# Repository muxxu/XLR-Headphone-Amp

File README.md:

## Symmetric XLR Headphone Amplifier

In this repo you will find a headphone amplifier mainly developed for in-ear monitoring.

The amplifier is designed to be driven with symmetrical audio signals connected via XLR. It converts the symmetrical signals (Left and Right for stereo or only Right for mono, switchable) to an unsymmetrical signal. This signal is further amplified to drive headphones or in-ears. Beside the complete eagle schematics and board files, the repo contains a 3D printable casing. It is designed so that it can be attached to your belt. The amplifier is powered by 2-AA battery cells. These should last easily 50 hours, so enough time for some band sessions or concerts.

If you are interested in building one or have any questions feel free to contact me.

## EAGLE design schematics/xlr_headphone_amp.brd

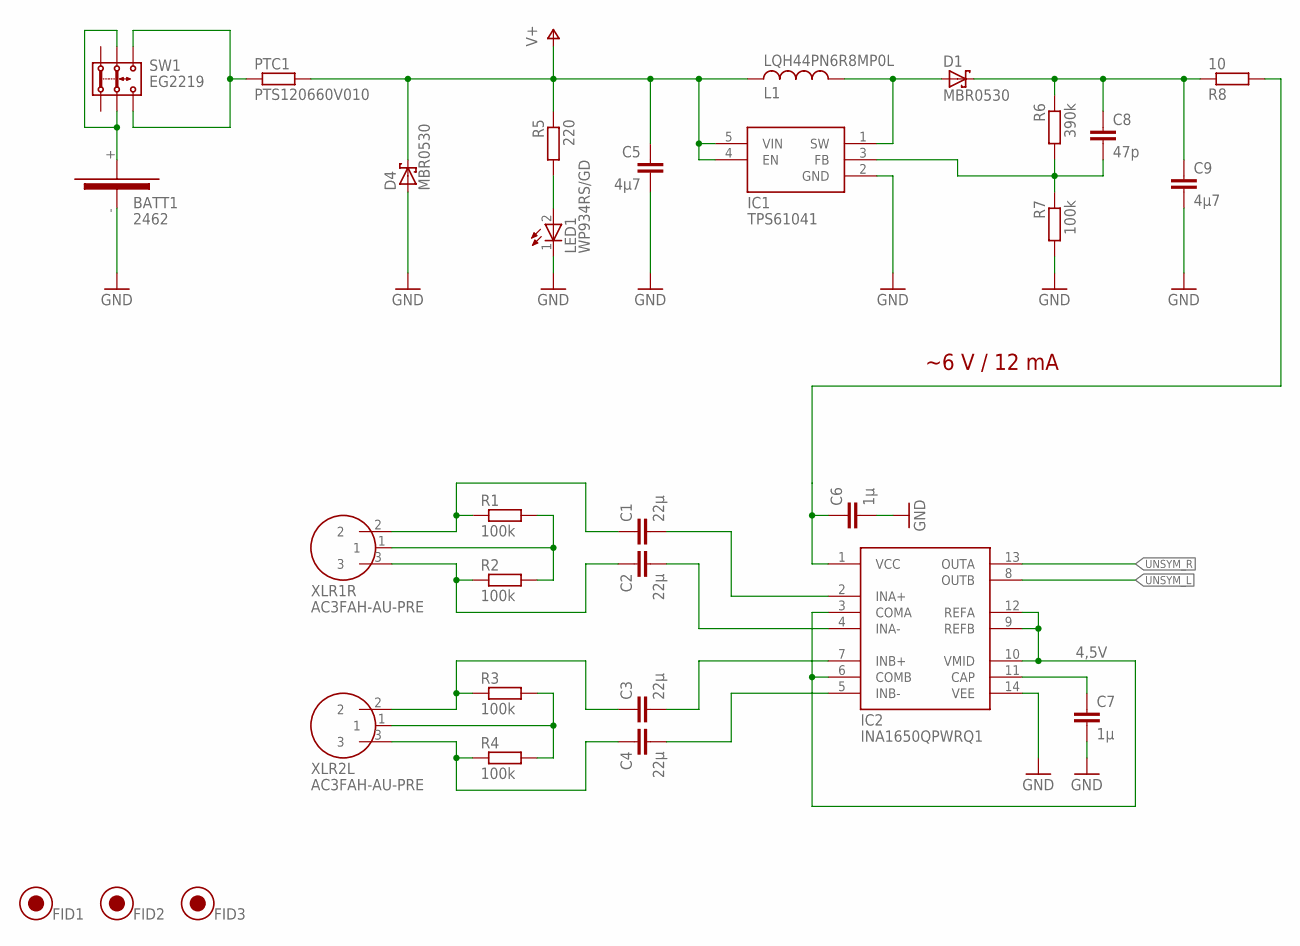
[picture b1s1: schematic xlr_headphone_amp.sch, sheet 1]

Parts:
BATT1: 2462
C1, C2, C3, C4: 22µ; C1206
C5, C9: 4µ7; C1206
C6, C7: 1µ; C1206
C8: 47p; C1206
D1, D4: MBR0530; SOD123
FID1, FID2, FID3: FIDICUAL
IC1: TPS61041; SOT23-5
IC2: INA1650QPWRQ1; R-PDSO-G14
L1: LQH44PN6R8MP0L; L1515(4040)
LED1: WP934RS/GD; WP934
PTC1: PTS120660V010; R1206
R1, R2, R3, R4, R7: 100k; R1206
R5: 220; R1206
R6: 390k; R1206
R8: 10; R1206
SW1: EG2219
XLR1R, XLR2L: AC3FAH-AU-PRE; AC3FAH

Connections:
4,5V: IC2.3 (COMA), IC2.6 (COMB), IC2.9 (REFB), IC2.10 (VMID), IC2.12 (REFA)
GND: BATT1.- (NEG), C5.2, C6.2, C7.2, C9.2, D4.A, IC1.2 (GND), IC2.14 (VEE), LED1.1 (C), R7.2; also elsewhere on the board
unnamed: R1.2, R2.2, XLR1R.1
unnamed: C1.1, R1.1, XLR1R.2
unnamed: C2.1, R2.1, XLR1R.3
unnamed: C1.2, IC2.2 (INA+)
unnamed: C2.2, IC2.4 (INA-)
unnamed: R3.2, R4.2, XLR2L.1
unnamed: C3.1, R3.1, XLR2L.2
unnamed: C4.1, R4.1, XLR2L.3
unnamed: C3.2, IC2.7 (INB+)
unnamed: C4.2, IC2.5 (INB-)
unnamed: C7.1, IC2.11 (CAP)
unnamed: LED1.2 (A), R5.2
unnamed: D1.A, IC1.1 (SW), L1.1
unnamed: C8.2, IC1.3 (FB), R6.2, R7.1
unnamed: C8.1, C9.1, D1.C, R6.1, R8.1
unnamed: BATT1.+ (POS), SW1.B1, SW1.B2
unnamed: PTC1.1, SW1.C1, SW1.C2
unnamed: C6.1, IC2.1 (VCC), R8.2
UNSYM_L: IC2.8 (OUTB); also elsewhere on the board
UNSYM_R: IC2.13 (OUTA); also elsewhere on the board
V+: C5.1, D4.C, IC1.4 (EN), IC1.5 (VIN), L1.2, PTC1.2, R5.1; also elsewhere on the board

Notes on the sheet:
~6 V / 12 mA

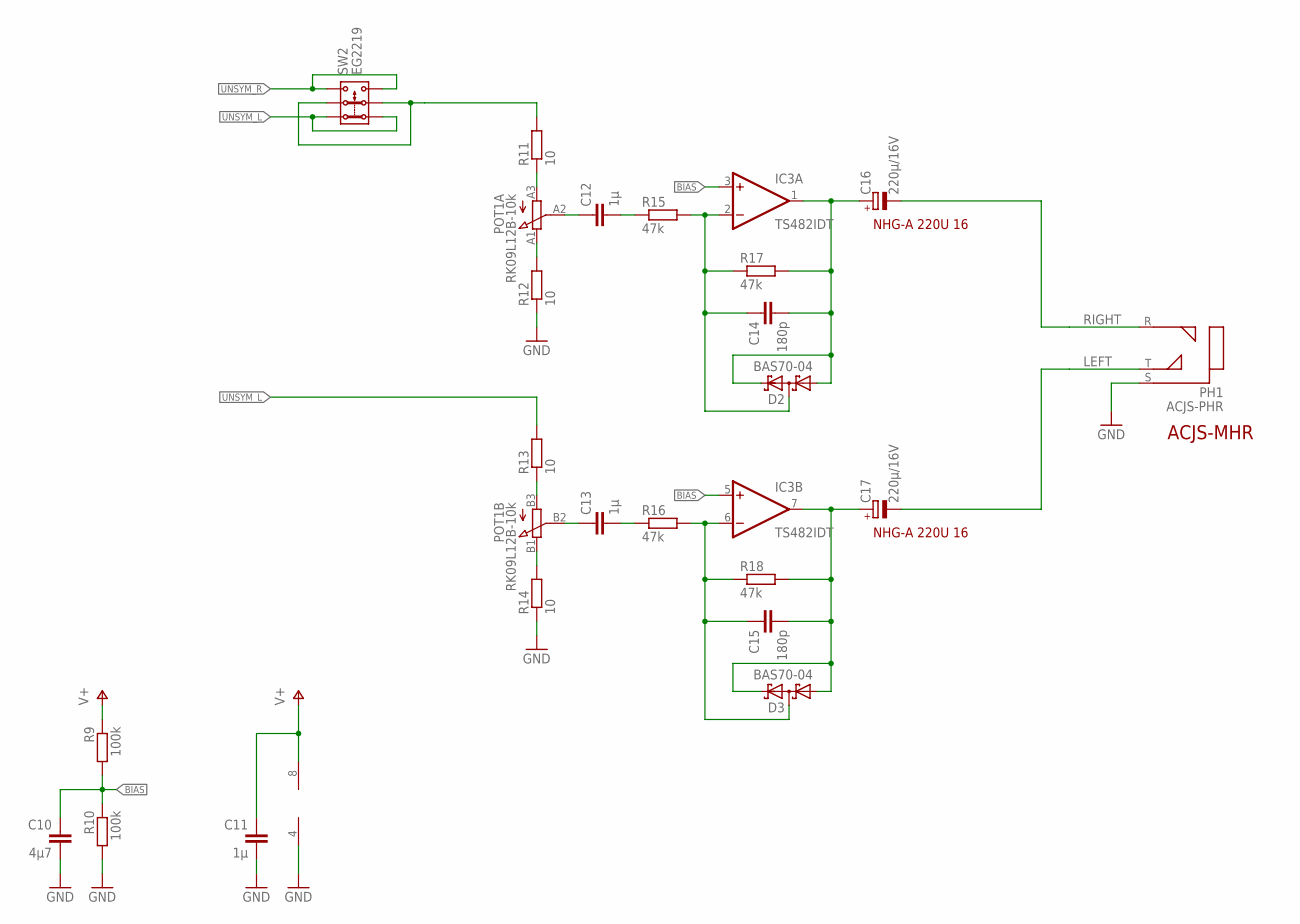
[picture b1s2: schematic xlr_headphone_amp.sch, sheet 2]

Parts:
C10: 4µ7; C1206
C11, C12, C13: 1µ; C1206
C14, C15: 180p; C1206
C16, C17: 220µ/16V; E2,5-6
D2, D3: BAS70-04; SOT23
IC3: TS482IDT; SO08
PH1: ACJS-PHR; ACJS
POT1: RK09L12B-10k; RK09L12
R9, R10: 100k; R1206
R11, R12, R13, R14: 10; R1206
R15, R16, R17, R18: 47k; R1206
SW2: EG2219

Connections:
BIAS: C10.1, IC3.3 (+IN), IC3.5 (+IN), R9.2, R10.1
GND: C10.2, C11.2, IC3.4 (V-), PH1.S, R10.2, R12.1, R14.1; also elsewhere on the board
LEFT: C17.-, PH1.T
unnamed: POT1.B1 (1), R14.2
unnamed: POT1.B3 (3), R13.1
unnamed: C14.1, D2.3 (C1A2), IC3.2 (-IN), R15.2, R17.1
unnamed: R11.2, SW2.B1, SW2.B2
unnamed: C13.1, POT1.B2 (2)
unnamed: POT1.A1 (1), R12.2
unnamed: C12.2, R15.1
unnamed: C12.1, POT1.A2 (2)
unnamed: C15.1, D3.3 (C1A2), IC3.6 (-IN), R16.2, R18.1
unnamed: C15.2, C17.+, D3.1 (A1), D3.2 (C2), IC3.7 (OUT), R18.2
unnamed: POT1.A3 (3), R11.1
unnamed: C13.2, R16.1
unnamed: C14.2, C16.+, D2.1 (A1), D2.2 (C2), IC3.1 (OUT), R17.2
RIGHT: C16.-, PH1.R
UNSYM_L: R13.2, SW2.A1, SW2.A2; also elsewhere on the board
UNSYM_R: SW2.C1, SW2.C2; also elsewhere on the board
V+: C11.1, IC3.8 (V+), R9.1; also elsewhere on the board

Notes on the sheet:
NHG-A 220U 16
ACJS-MHR

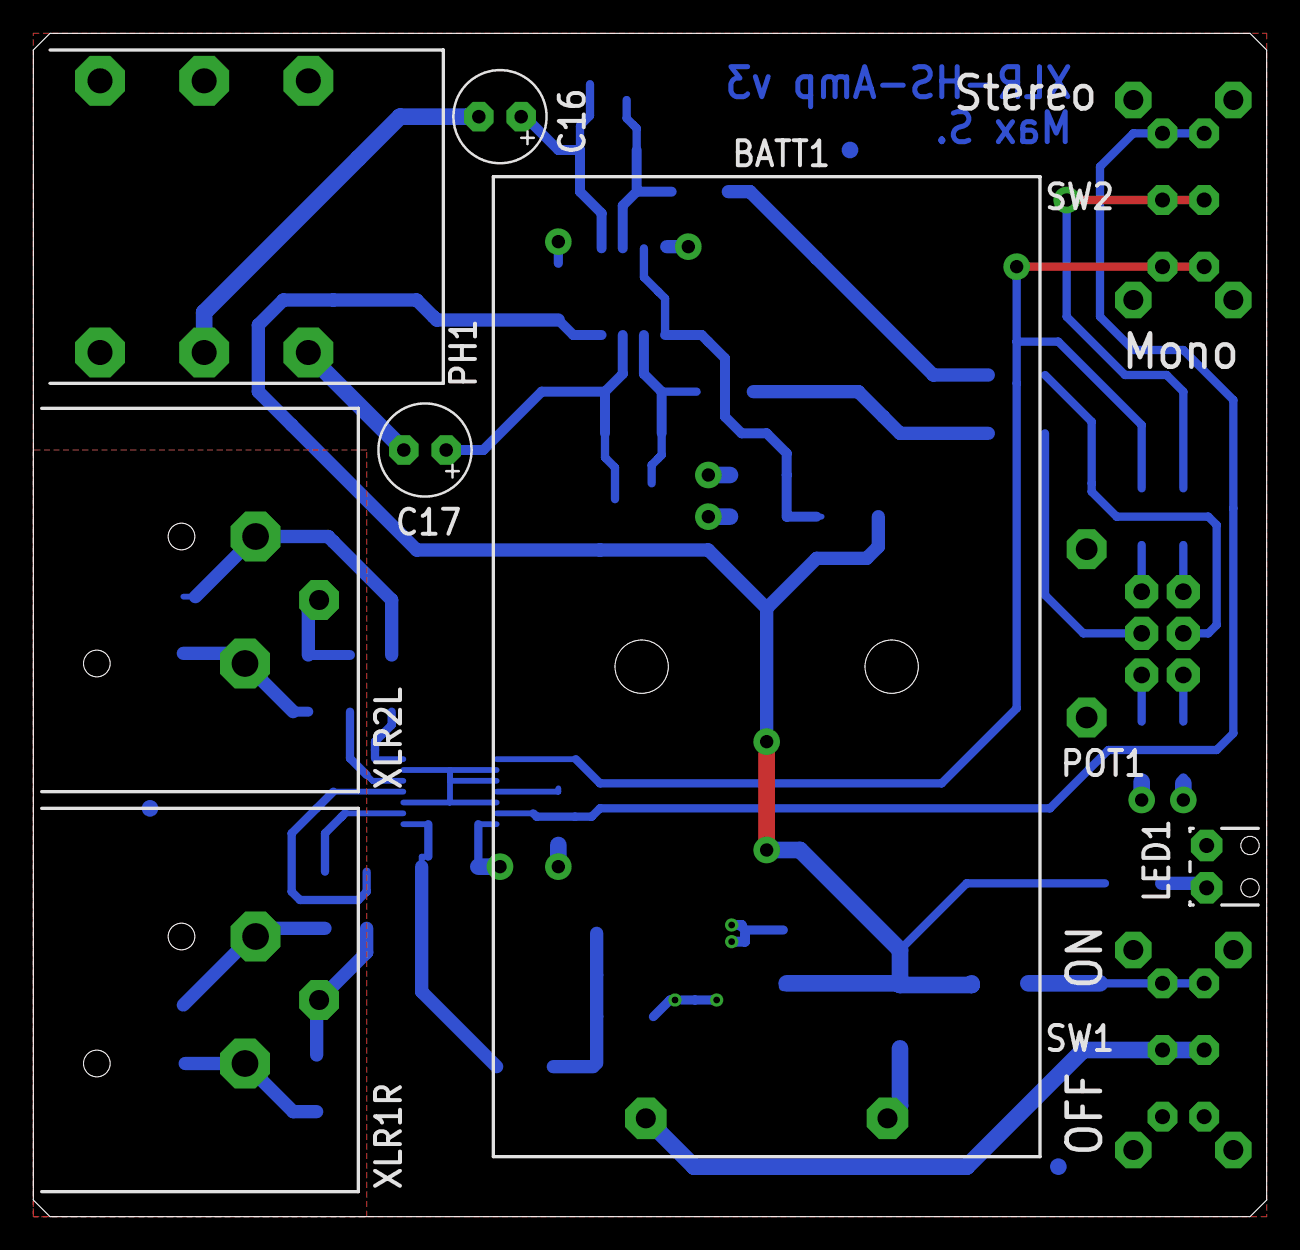
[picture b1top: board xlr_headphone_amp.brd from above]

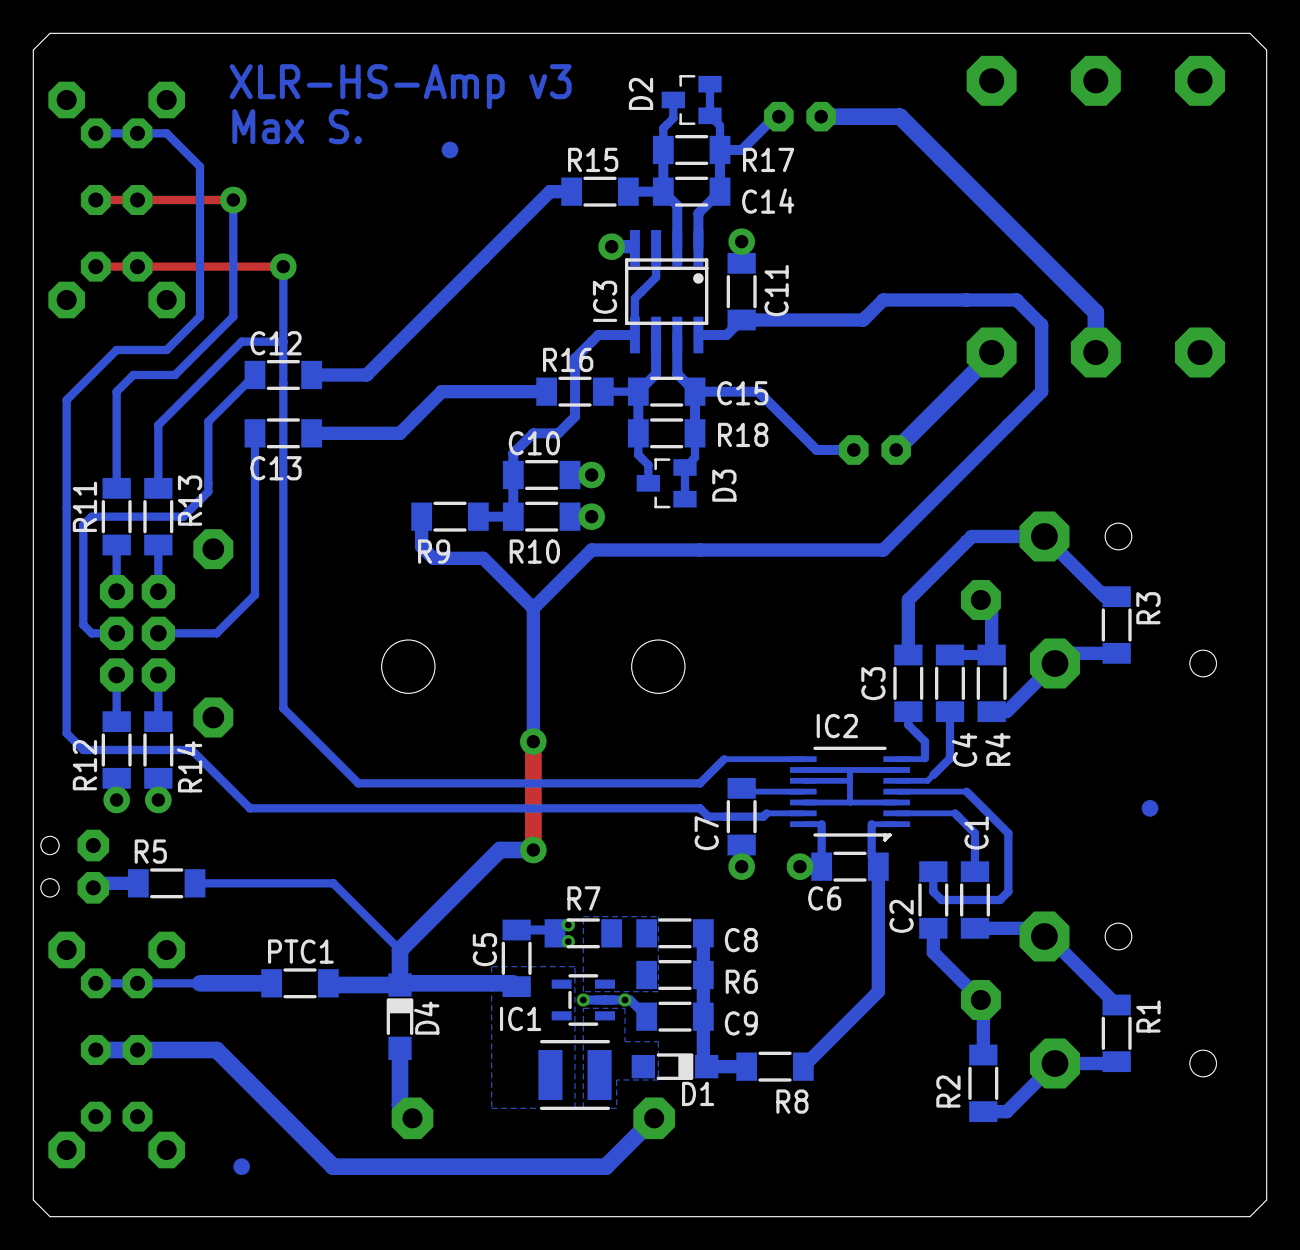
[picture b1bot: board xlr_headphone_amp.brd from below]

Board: 2 copper layers, 74.0 x 71.0 mm, 55 parts (45 on the bottom side), 39 nets.

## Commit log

2023-08-08 minor changes
